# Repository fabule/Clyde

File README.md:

Clyde
======
Clyde is a lamp with a lot of personality that you can adapt, play with, and truly call your own. Clyde is open source and Arduino-compatible.  You can change how Clyde reacts to his environment by inserting personality modules on his main controller board. You can also change how Clyde behaves by reprogramming his firmware using the standard Arduino IDE.

For more information, see the website at: http://www.fabule.com or the forum at: http://fabule.com/forum/

To report a bug in the hardware or software, go to:
http://github.com/fabule/Clyde/issues

Installation
------------

The Clyde firmware is divided into three parts: bootloader, library, and sketch.

You can find the Clyde library in /software/arduino/libraries/. Place the "Clyde" library folder inside your Arduino "librairies" folder. This contains the majority of the code that controls Clyde. If you are not sure about how to install an Arduino library, you can find instructions here: http://arduino.cc/en/Guide/Libraries

When the library is in place, you can look for the sketch in /software/arduino/libraries/Clyde/Examples/ClydeOriginal. This sketch does not contain much, but it is a good place to start playing with Clyde's behaviors.

If you are using Windows, you'll need to install Clyde's driver. Find installers for 32-bit and 64-bit in /software/arduino/drivers/.  Double-click the driver that matches your needs.

Before you open your Arduino IDE, you'll need to copy one more folder. This step will add Clyde as a device under the "Tools > Board menu". First, if you do not have a "hardware" folder at the same level as your Arduino "librairies" folder, time to create one. Browse to the "hardware" folder in /software/arduino/hardware/ and open the subfolder that matches the version of your Arduino IDE, 1.0.5 or 1.5. Inside you'll find a "fabule" folder. Copy the "fabule" folder, inside the Arduino "hardware" folder you just created.

At this point, you should be ready to compile and upload Clyde's firmware. Connect Clyde to your computer using the USB cable.  Open the "ClydeFirmware" sketch in your Arduino IDE under "File > Examples > Clyde > ClydeOriginal" . Select Clyde under the "Tools > Board" menu, and the port assigned to Clyde under "Tools > Serial" Port. Press "Upload", and the firmware should compile and upload into Clyde.

If you want to make modifications to the bootloader, please refer to the information found here: https://github.com/fabule/Clyde/tree/master/software/arduino/bootloaders/caterina

Configurations
--------------

### Using `TimeAlarms` library to enable alarms

The `Time` and `TimeAlarms` libraries provide functionality to set/get the time on an arduino and enable repeated or single alarms. An example configuration to use Clyde as an *alarm clock* is given in `/software/arduino/libraries/Clyde/Examples/ClydeTimeAlarm.ino`. This firmware can be uploaded instead of the `ClydeOriginal` firmware above by loading it under "File > Examples > Clyde > ClideTimeAlarms" and following the steps described above to compile and upload the firmware. The essential configuration steps for this alternative firmware are to set the time and to define an alarm. Without any additional hardware, the time has to be set manually in and the firmware has to be uploaded to Clyde each time Clyde is detached from the power source. In principle, the `Time` and `TimeAlarms` would allow to synchronize the arduino time e.g. with internet time over a Wifi shield.

### Using Clyde without the eye

The eye of some Clydes can become quite buggy after some time. Thus, the preprocessor variable `ENABLE_EYE` has been included, that, if not defined allows to switch the lights by touching one of the legs of Clyde (requires the TouchyFeely module). The `ENABLE_EYE` can be set in the `Clyde.h` file, the leg that is to be used as a switch can be defined with the `LEG_SWITCH` variable in `ClydeTouchyFeely.cpp`.

Credits
-------
Clyde is an open source project manage by Fabule Fabrications in Montréal, Québec, Canada.

Clyde is based on the Arduino project, see the website at: http://arduino.cc

Arduino uses the GNU avr-gcc toolchain, avrdude, avr-libc, and code from
Processing and Wiring, LUFA, and i2cdevlib.

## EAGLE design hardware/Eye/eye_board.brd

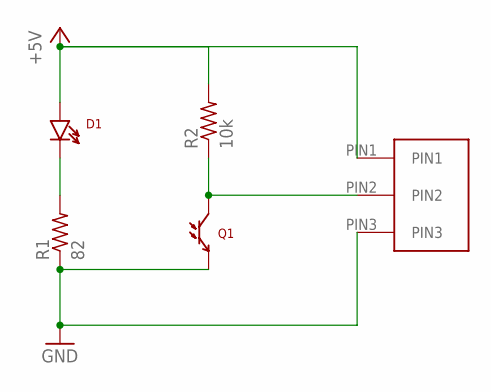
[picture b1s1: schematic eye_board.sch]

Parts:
3PIN_CONN: XH_JST_CONN_3POS_TOP
D1: LTE-302
Q1: LTR-301
R1: 82; R0603
R2: 10k; R0805

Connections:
+5V: 3PIN_CONN.PIN1, D1.A, R2.2
GND: 3PIN_CONN.PIN3, Q1.E, R1.1
unnamed: D1.C, R1.2
unnamed: 3PIN_CONN.PIN2, Q1.C, R2.1

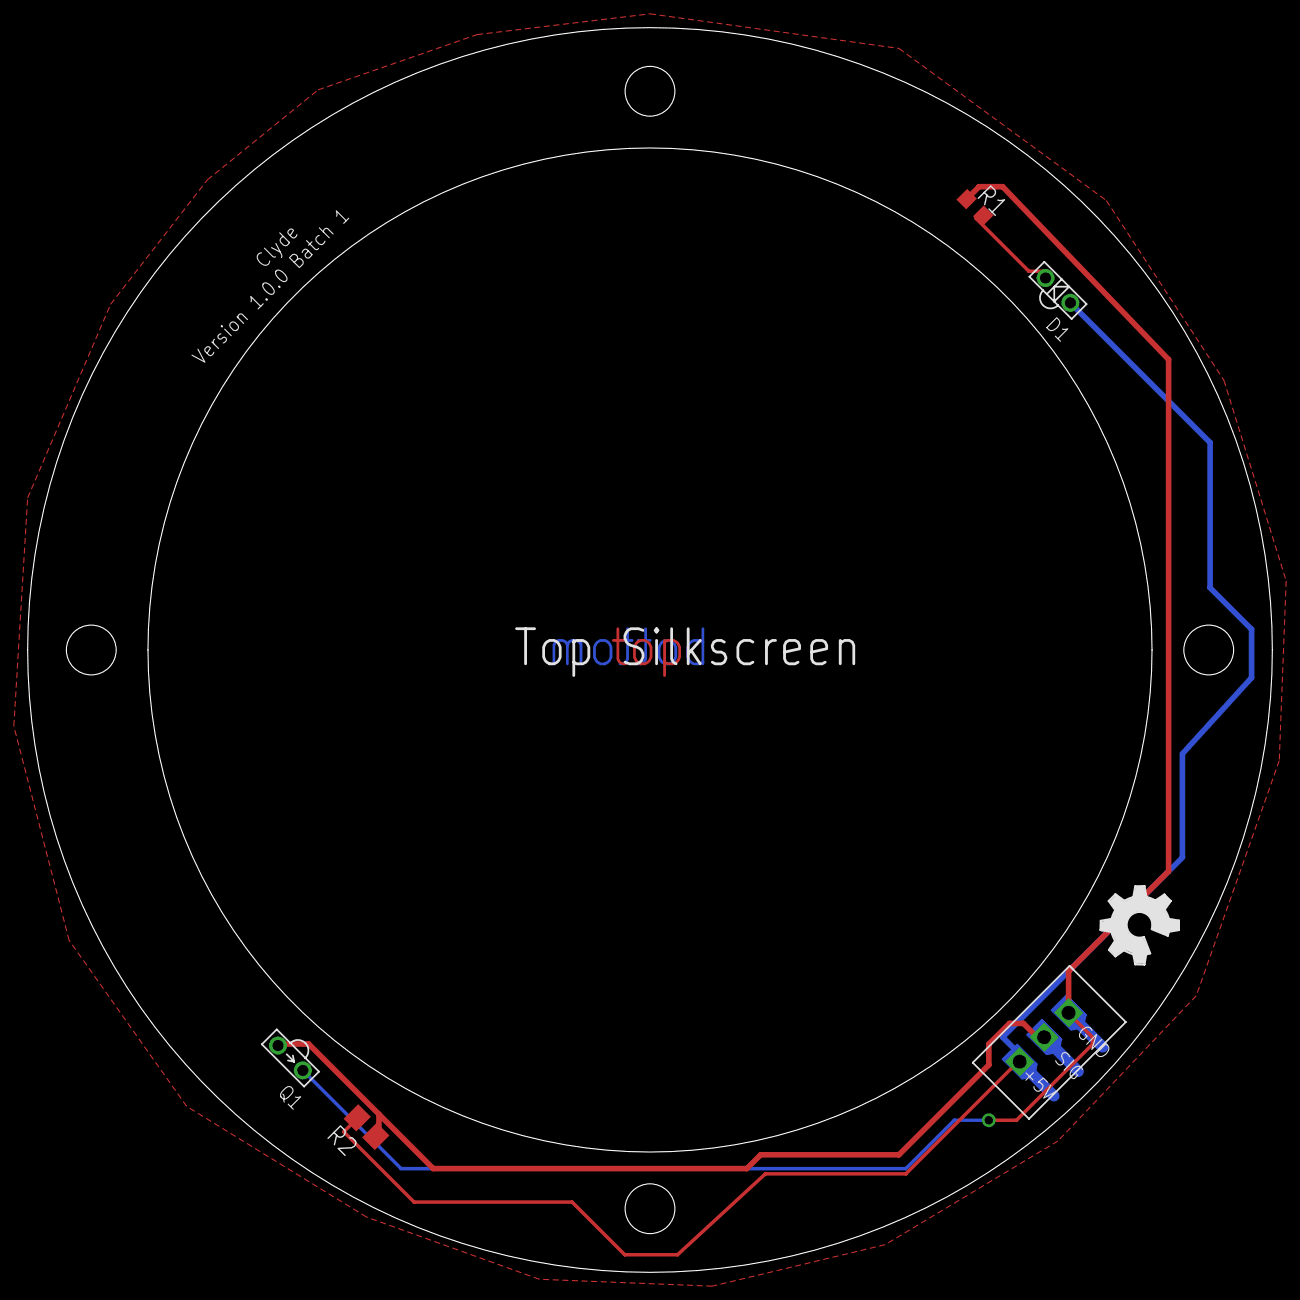
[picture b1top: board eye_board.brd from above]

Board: 2 copper layers, 90.0 x 90.0 mm, 6 parts (0 on the bottom side), 4 nets.

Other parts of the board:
U$2: OSHW_FILLX200_NOTEXT

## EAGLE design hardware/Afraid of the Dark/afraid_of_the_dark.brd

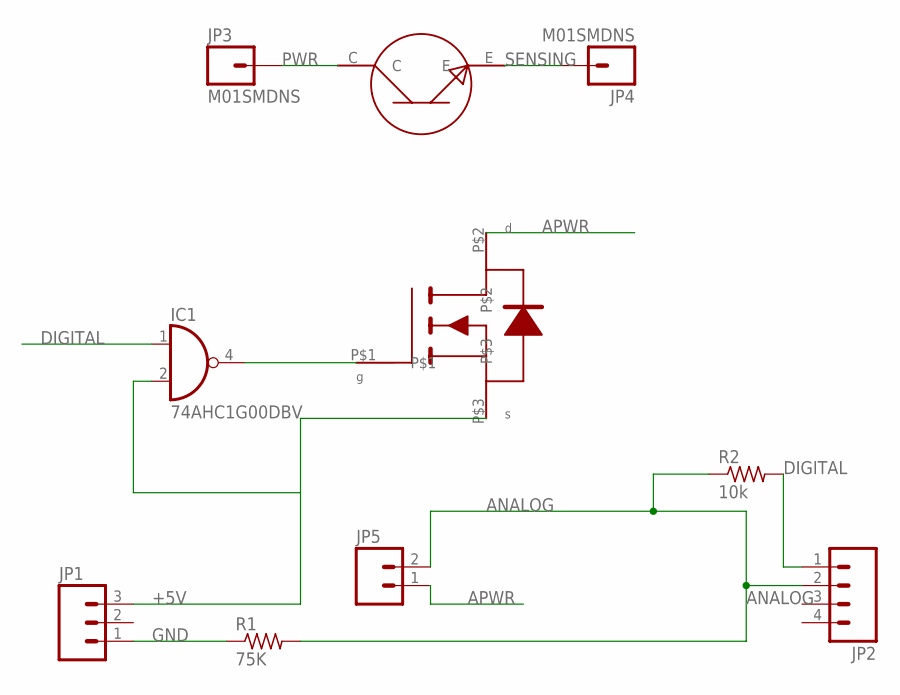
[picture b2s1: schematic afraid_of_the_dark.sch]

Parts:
IC1: 74AHC1G00DBV; SOT23-5
JP1: M03PTH; 1X03
JP2: M04PTH; 1X04
JP3, JP4: M01SMDNS; 1X01NS
JP5: M023.5MM; SCREWTERMINAL-3.5MM-2
R1: 75K; R0805
R2: 10k; R0805
U1: AMBIENT_LIGHT_SENSOR
U3: SI2302DS_MOSFET

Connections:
+5V: IC1.2 (I1), JP1.3, U3.P$3
ANALOG: JP2.2, JP5.2, R1.2, R2.1
APWR: JP5.1, U3.P$2
DIGITAL: IC1.1 (I0), JP2.1, R2.2
GND: IC1.3 (GND), JP1.1, R1.1
unnamed: IC1.4 (O), U3.P$1
PWR: JP3.1, U1.C
SENSING: JP4.1, U1.E
VCC: IC1.5 (VCC)

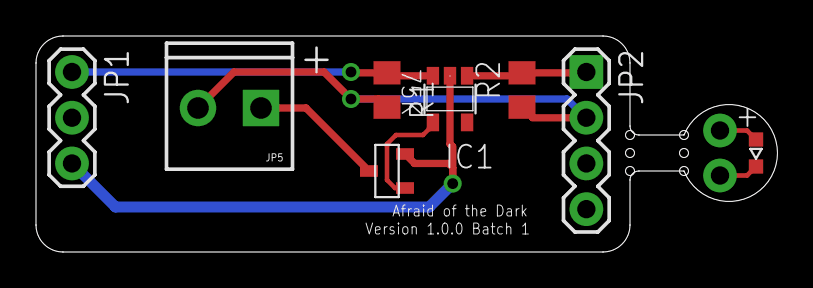
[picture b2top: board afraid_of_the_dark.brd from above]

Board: 2 copper layers, 41.2 x 12.0 mm, 11 parts (1 on the bottom side), 8 nets.

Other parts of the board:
U$2: OSHW_FILLX200_NOTEXT

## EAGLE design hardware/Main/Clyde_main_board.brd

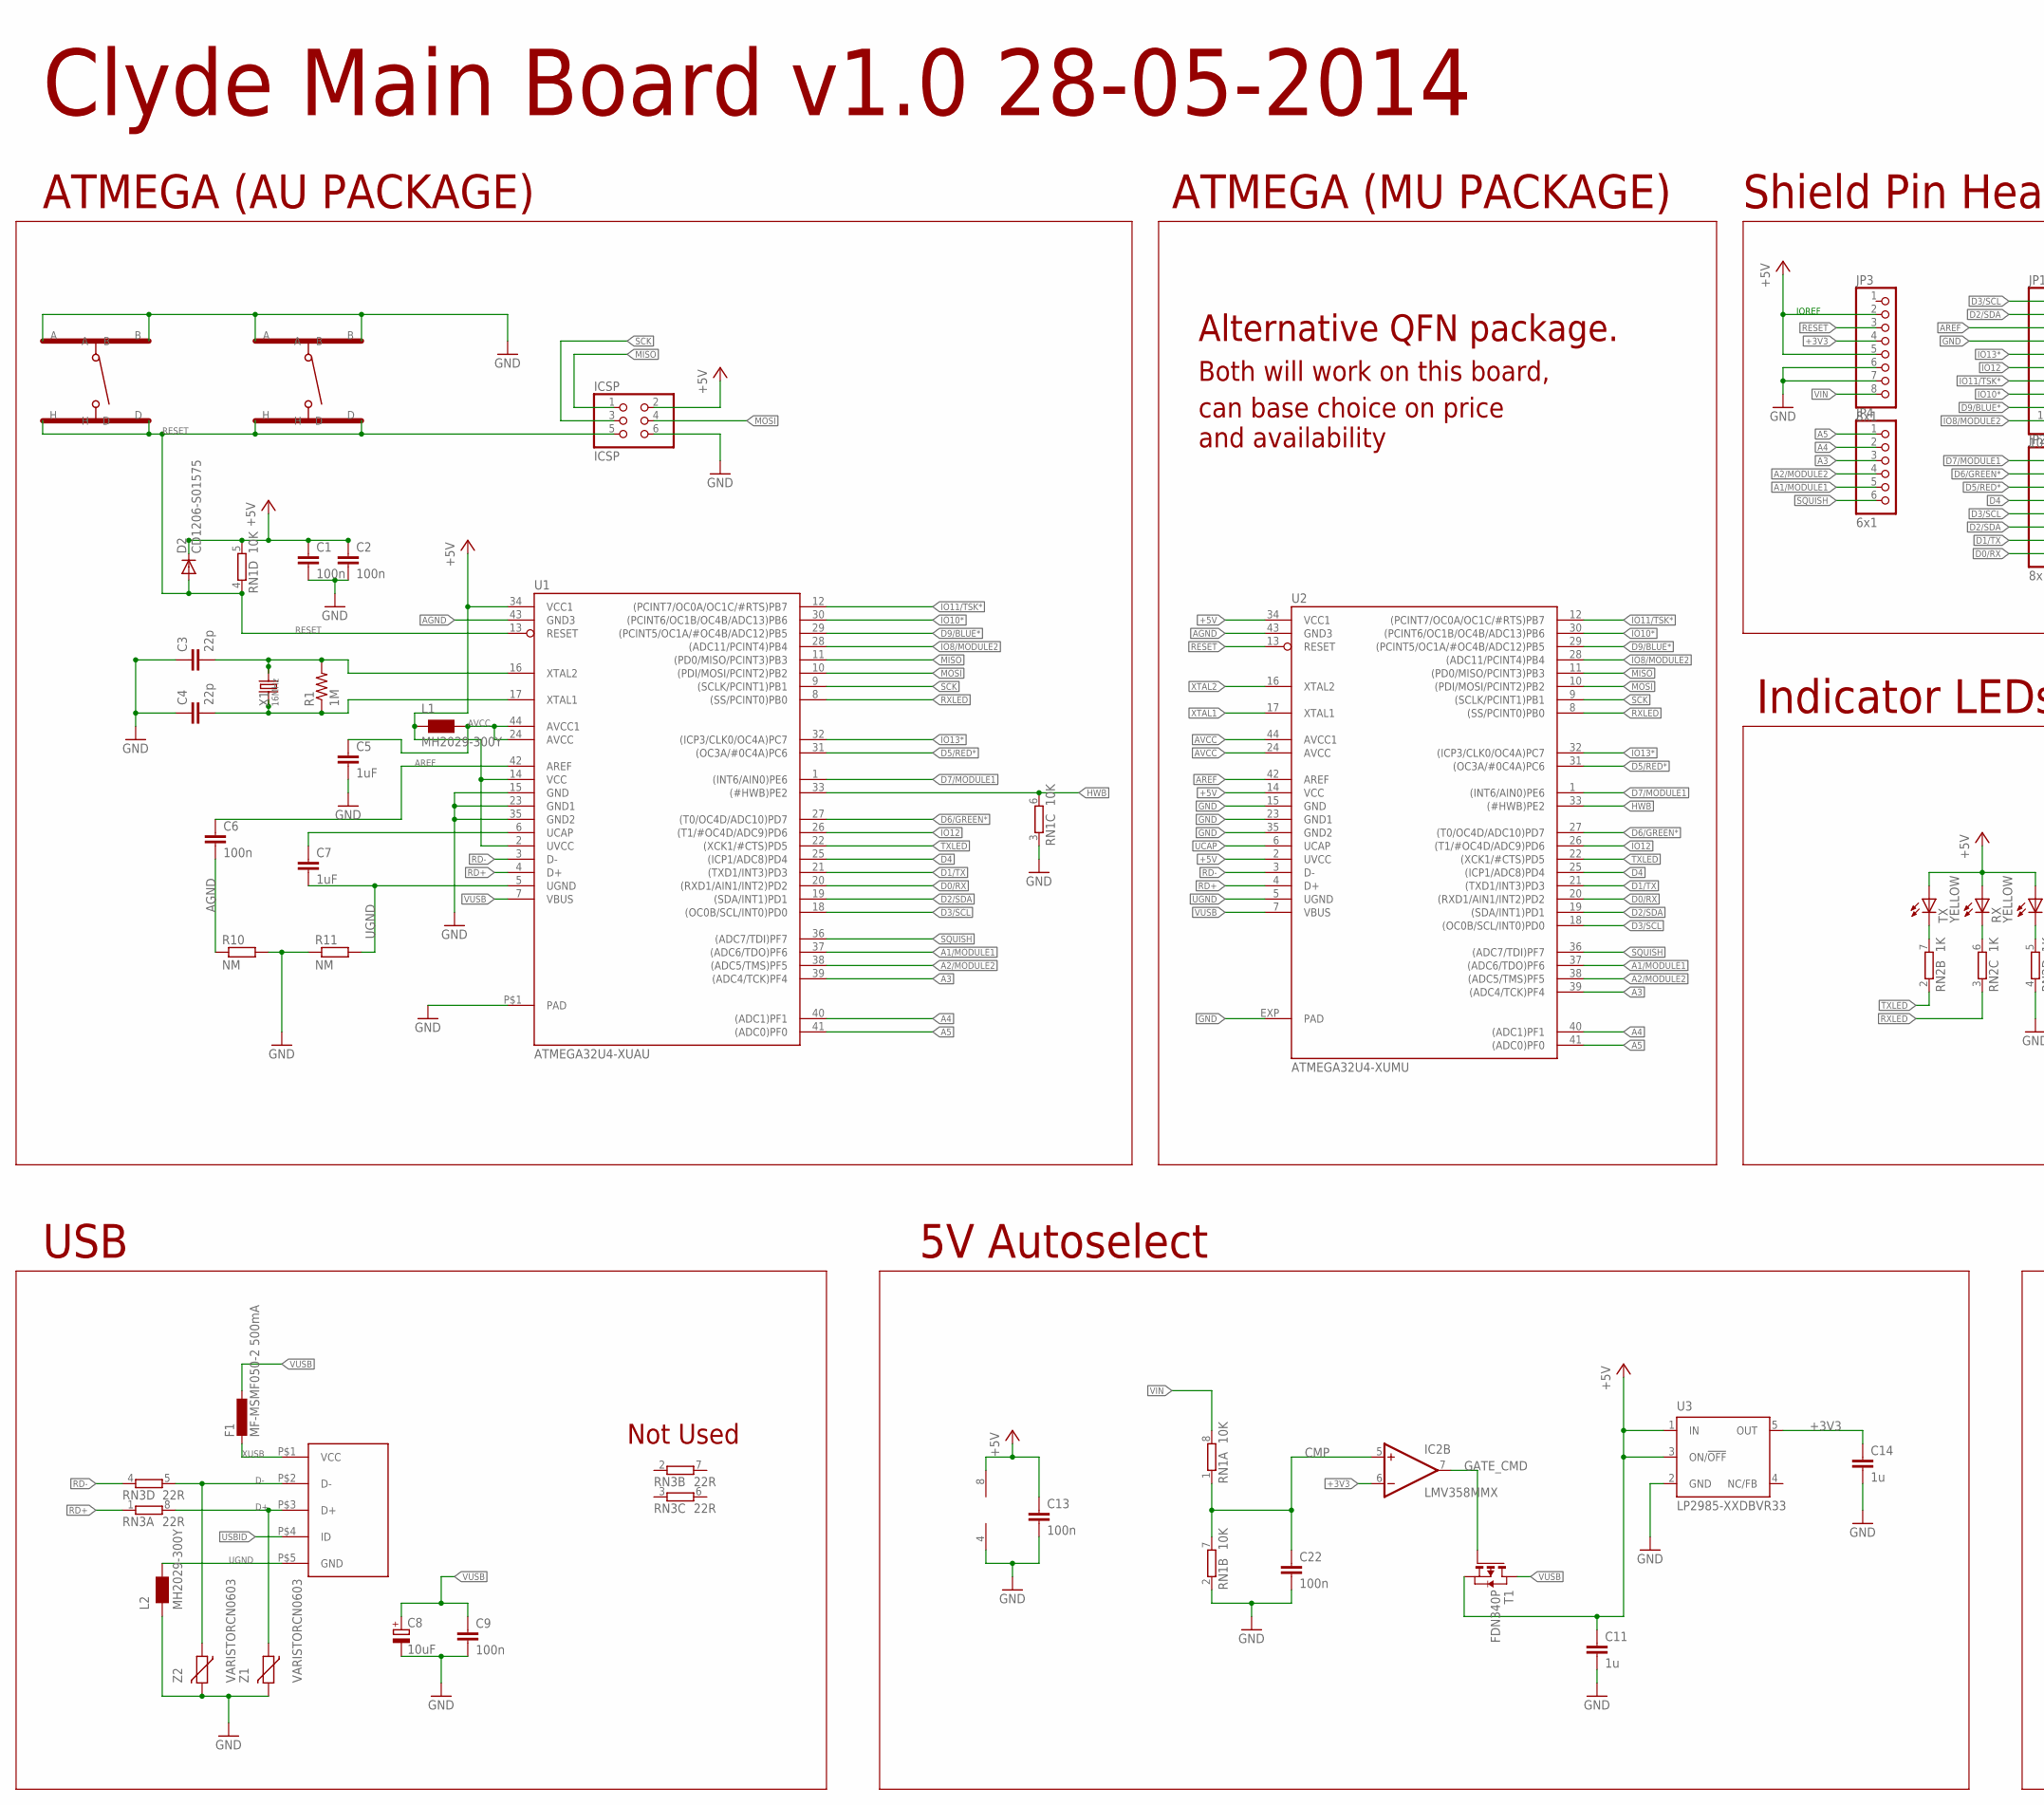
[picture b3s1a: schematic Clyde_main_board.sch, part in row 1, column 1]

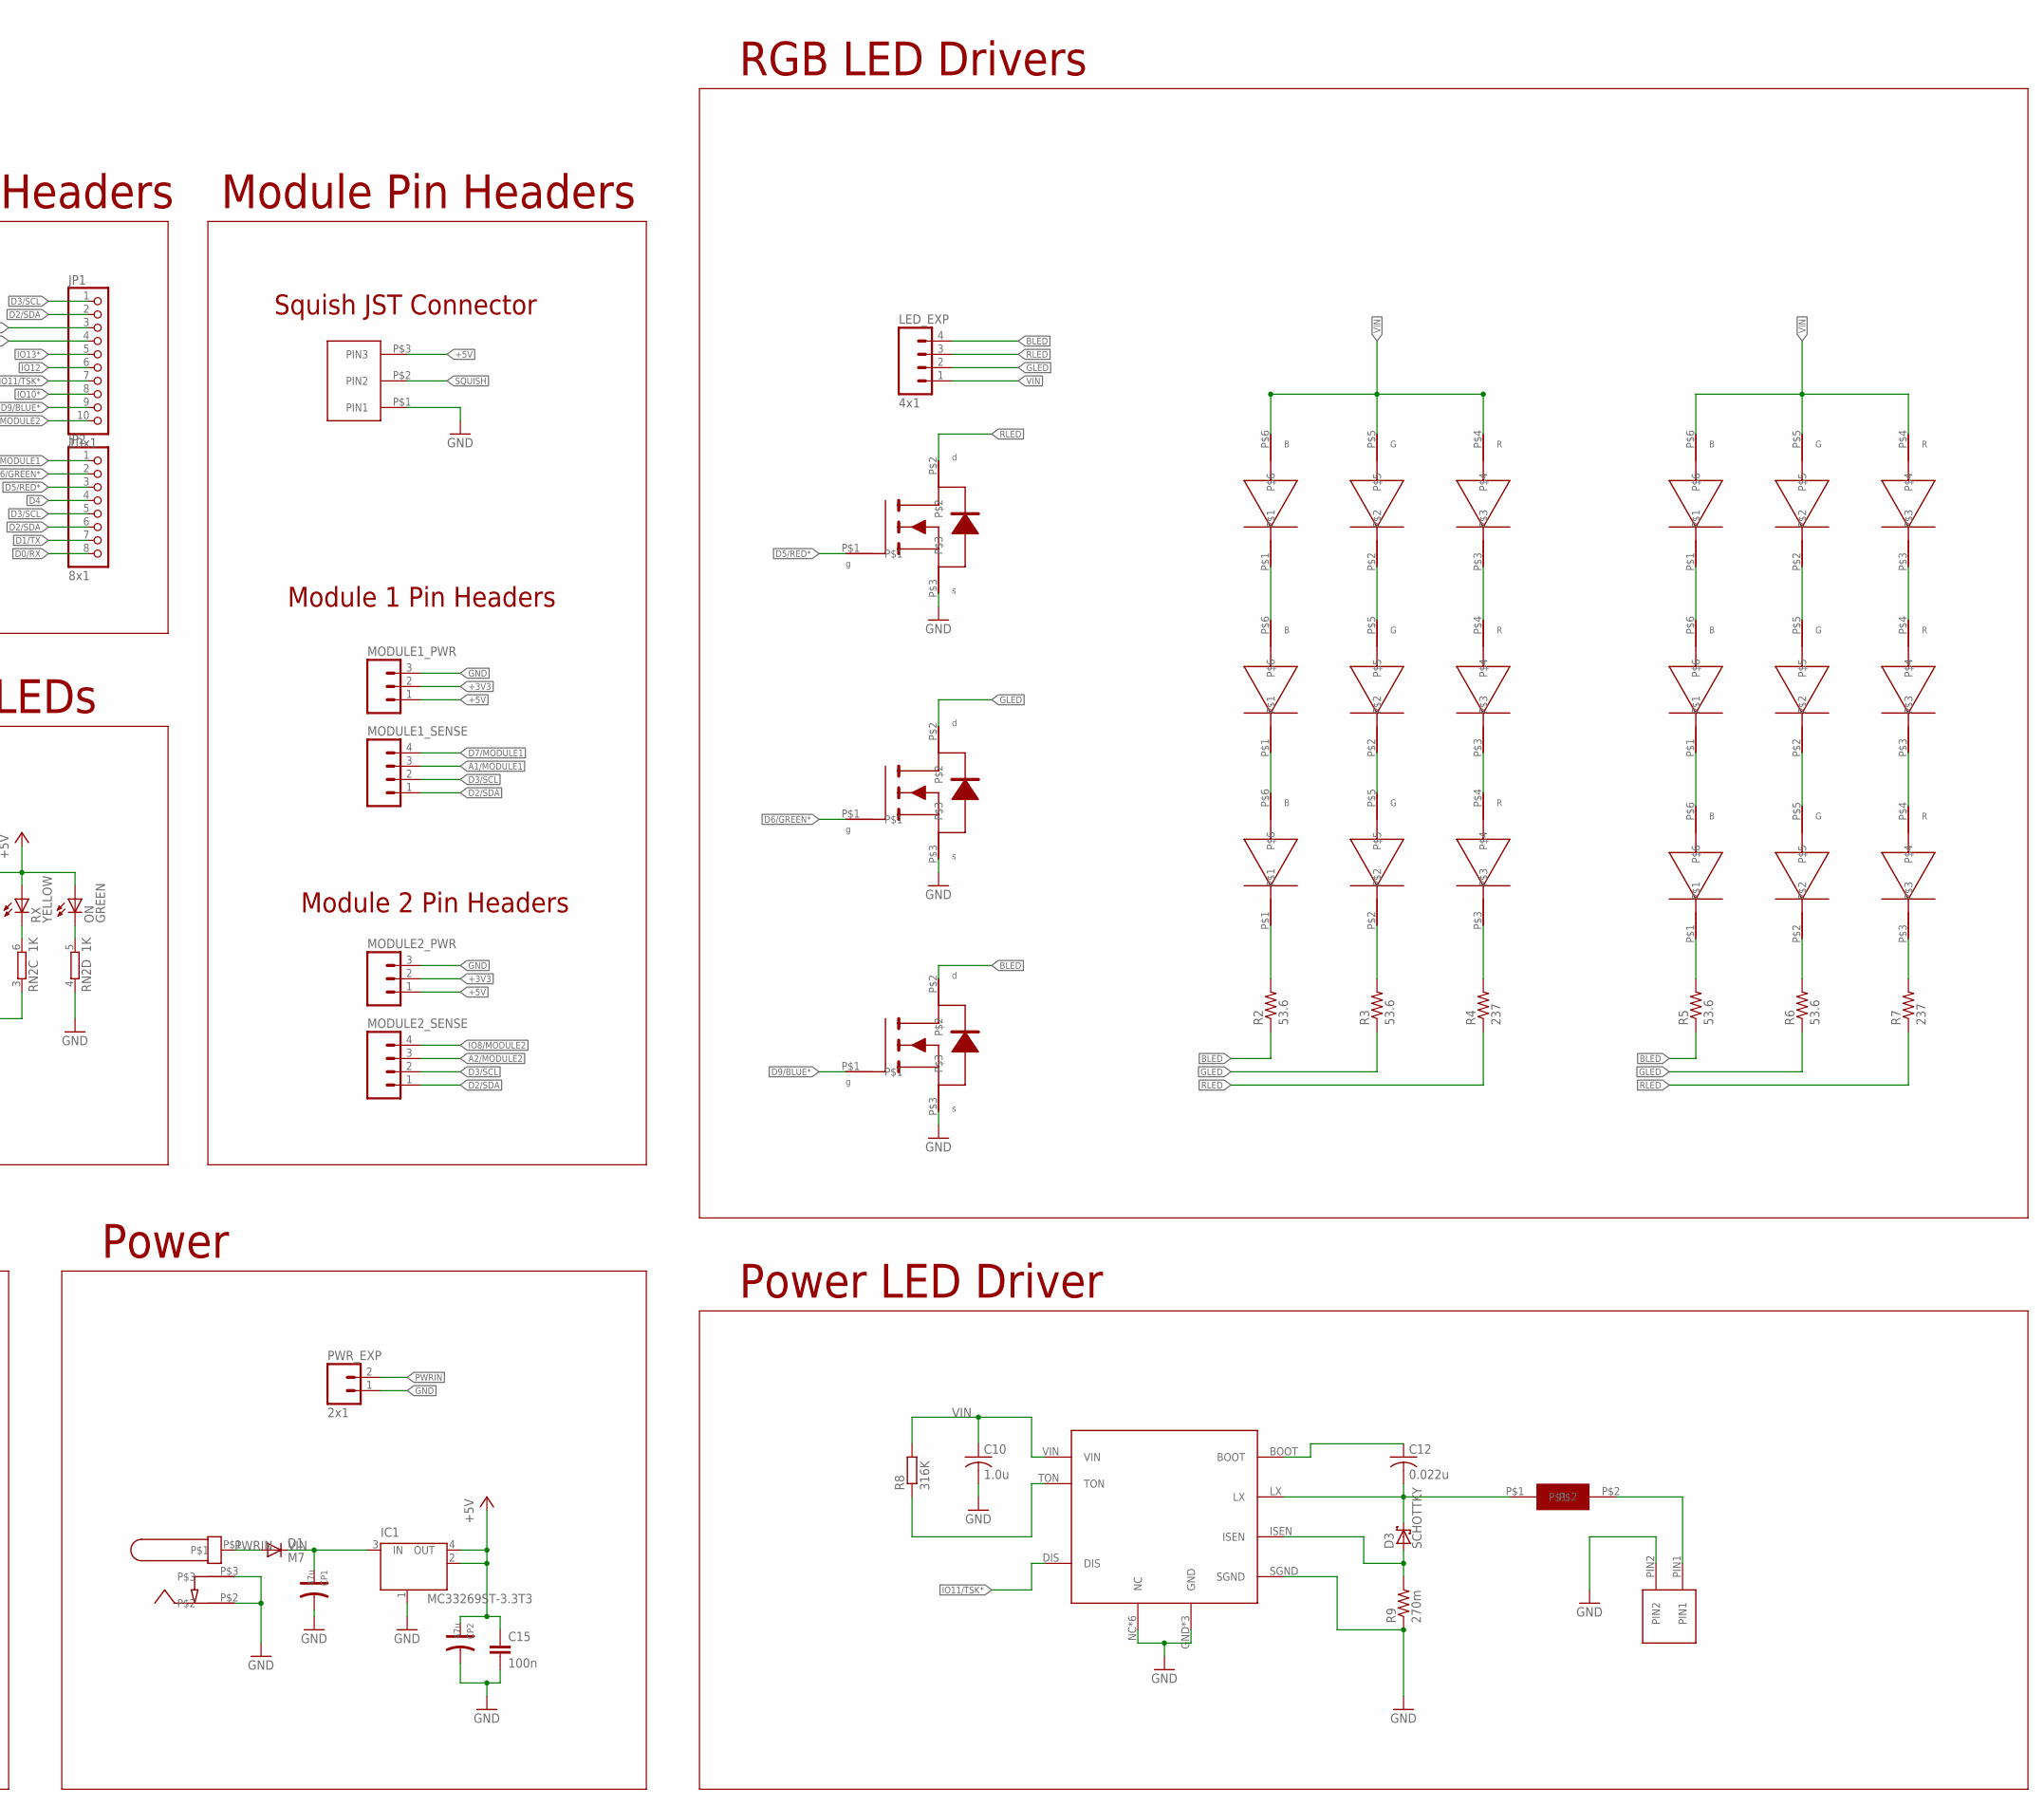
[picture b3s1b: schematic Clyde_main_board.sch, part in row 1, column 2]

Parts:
2PIN_CONN: XH_JST_CONN_2POS_TOP
C1, C2, C6, C9, C13, C15, C22: 100n; C0603-ROUND
C3, C4: 22p; C0603-ROUND
C5, C7: 1uF; C0603-ROUND
C8: 10uF; SMC_B
C10: 1.0u; C1210
C11, C14: 1u; C0603-ROUND
C12: 0.022u; C0805
CP1, CP2: 47u; ELECTRO-SMD-C-6MM
D1: M7; SMB
D2: CD1206-S01575; MINIMELF
D3: SCHOTTKY; SMB
F1: MF-MSMF050-2 500mA; L1812
IC1: MC33269ST-3.3T3; SOT223
IC2: LMV358MMX; MSOP08
ICSP: ICSP; 2X03
IR_CONNECT: XH_JST_CONN_3POS_SIDE_SMT
I_LEDDRIVER: TAIYO_YUDEN_6045_INDUCTOR
J1: MOLEX_VERT_MINIUSB
JP1: 10x1; 1X10
JP2, JP3: 8x1; 1X08
JP4: 6x1; 1X06
L1, L2: MH2029-300Y; 0805
LED_EXP: 4x1; 1X04_LONGPADS
MODULE1_PWR, MODULE2_PWR: M03PTH; 1X03
MODULE1_SENSE, MODULE2_SENSE: M04PTH; 1X04
ON: GREEN; CHIPLED_0603
PWR_EXP: 2x1; SCREWTERMINAL-3.5MM-2
PWR_JACK: VERT_PWRJACK_PJ-006A_CUIINC
R1: 1M; 0805
R2, R3, R5, R6: 53.6; R0603
R4, R7: 237; R0603
R8: 316K; R0603-ROUND
R9: 270m; R0805
R10, R11: NM; R0402_NM
RGB1, RGB2, RGB3, RGB4, RGB5, RGB6: HANGZHOU_MULTICOLOR_3535WSA; HANGZHOU_MULTCOLOR_3535WSZ
RN1: 10K; CAY16
RN2: 1K; CAY16
RN3: 22R; CAY16
RST, RST1: COMAX_MINISWITCH
RX: YELLOW; CHIPLED_0603
T1: FDN340P; SOT-23
TBLUE: SI2302DS_MOSFET
TGREEN: SI2302DS_MOSFET
TRED: SI2302DS_MOSFET
TX: YELLOW; CHIPLED_0603
U1: ATMEGA32U4-XUAU; TQFP44-PAD
U2: ATMEGA32U4-XUMU; QFN44ML7X7
U3: LP2985-XXDBVR33; SOT23-DBV
U4: ALLEGRO_A6210
X1: 16MHz; XTAL_THRU_SMT
Z1, Z2: VARISTORCN0603; CT/CN0603

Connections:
+3V3: C14.1, IC2.6 (-IN), JP3.4, MODULE1_PWR.2, MODULE2_PWR.2, U3.5 (OUT)
+5V: C1.1, C2.1, C11.1, C13.1, C15.1, CP2.+, D2.C, IC1.2 (OUT), IC1.4 (OUT), IC2.8 (V+), ICSP.2, IR_CONNECT.P$3 (PIN3), JP3.2, JP3.5, L1.1, MODULE1_PWR.1, MODULE2_PWR.1, ON.A, RN1.5 (2), RX.A, T1.2 (S), TX.A, U1.2 (UVCC), U1.14 (VCC), U1.34 (VCC1), U2.2 (UVCC), U2.14 (VCC), U2.34 (VCC1), U3.1 (IN), U3.3 (ON/!OFF)
A1/MODULE1: JP4.5, MODULE1_SENSE.3, U1.37 ((ADC6/TDO)PF6), U2.37 ((ADC6/TDO)PF6)
A2/MODULE2: JP4.4, MODULE2_SENSE.3, U1.38 ((ADC5/TMS)PF5), U2.38 ((ADC5/TMS)PF5)
A3: JP4.3, U1.39 ((ADC4/TCK)PF4), U2.39 ((ADC4/TCK)PF4)
A4: JP4.2, U1.40 ((ADC1)PF1), U2.40 ((ADC1)PF1)
A5: JP4.1, U1.41 ((ADC0)PF0), U2.41 ((ADC0)PF0)
AGND: C6.2, R10.1, U1.43 (GND3), U2.43 (GND3)
AREF: C6.1, JP1.3, U1.42 (AREF), U2.42 (AREF)
AVCC: C5.1, L1.2, U1.24 (AVCC), U1.44 (AVCC1), U2.24 (AVCC), U2.44 (AVCC1)
BLED: LED_EXP.4, R2.1, R5.1, TBLUE.P$2
CMP: C22.1, IC2.5 (+IN), RN1.1, RN1.7 (2)
D0/RX: JP2.8, U1.20 ((RXD1/AIN1/INT2)PD2), U2.20 ((RXD1/AIN1/INT2)PD2)
D1/TX: JP2.7, U1.21 ((TXD1/INT3)PD3), U2.21 ((TXD1/INT3)PD3)
D2/SDA: JP1.2, JP2.6, MODULE1_SENSE.1, MODULE2_SENSE.1, U1.19 ((SDA/INT1)PD1), U2.19 ((SDA/INT1)PD1)
D3/SCL: JP1.1, JP2.5, MODULE1_SENSE.2, MODULE2_SENSE.2, U1.18 ((OC0B/SCL/INT0)PD0), U2.18 ((OC0B/SCL/INT0)PD0)
D4: JP2.4, U1.25 ((ICP1/ADC8)PD4), U2.25 ((ICP1/ADC8)PD4)
D5/RED*: JP2.3, TRED.P$1, U1.31 ((OC3A/#0C4A)PC6), U2.31 ((OC3A/#0C4A)PC6)
D6/GREEN*: JP2.2, TGREEN.P$1, U1.27 ((T0/OC4D/ADC10)PD7), U2.27 ((T0/OC4D/ADC10)PD7)
D7/MODULE1: JP2.1, MODULE1_SENSE.4, U1.1 ((INT6/AIN0)PE6), U2.1 ((INT6/AIN0)PE6)
D9/BLUE*: JP1.9, TBLUE.P$1, U1.29 ((PCINT5/OC1A/#OC4B/ADC12)PB5), U2.29 ((PCINT5/OC1A/#OC4B/ADC12)PB5)
D+: J1.P$3 (D+), RN3.8 (2), Z1.1
D-: J1.P$2 (D-), RN3.5 (2), Z2.1
GATE_CMD: IC2.7 (OUT), T1.3 (G)
GLED: LED_EXP.2, R3.1, R6.1, TGREEN.P$2
GND: 2PIN_CONN.PIN2, C1.2, C2.2, C3.1, C4.1, C5.2, C8.-, C9.2, C10.2, C11.2, C13.2, C14.2, C15.2, C22.2, CP1.-, CP2.-, IC1.1 (GND/ADJ), IC2.4 (V-), ICSP.6, IR_CONNECT.P$1 (PIN1), JP1.4, JP3.6, JP3.7, L2.1, MODULE1_PWR.3, MODULE2_PWR.3, PWR_EXP.1, PWR_JACK.P$2, PWR_JACK.P$3, R9.1, R10.2, R11.1, RN1.2 (1), RN1.3 (1), RN2.4 (1), RST.A, RST.B, RST1.A, RST1.B, TBLUE.P$3, TGREEN.P$3, TRED.P$3, U1.15 (GND), U1.23 (GND1), U1.35 (GND2), U1.P$1 (PAD), U2.15 (GND), U2.23 (GND1), U2.35 (GND2), U2.EXP (PAD), U3.2 (GND), U4.GND, U4.GND1 (GND), U4.GND2 (GND), U4.NC, U4.NC1 (NC), U4.NC2 (NC), U4.NC3 (NC), U4.NC4 (NC), U4.NC5 (NC), U4.SGND, Z1.2, Z2.2
HWB: RN1.6 (2), U1.33 ((#HWB)PE2), U2.33 ((#HWB)PE2)
IO8/MODULE2: JP1.10, MODULE2_SENSE.4, U1.28 ((ADC11/PCINT4)PB4), U2.28 ((ADC11/PCINT4)PB4)
IO10*: JP1.8, U1.30 ((PCINT6/OC1B/OC4B/ADC13)PB6), U2.30 ((PCINT6/OC1B/OC4B/ADC13)PB6)
IO11/TSK*: JP1.7, U1.12 ((PCINT7/OC0A/OC1C/#RTS)PB7), U2.12 ((PCINT7/OC0A/OC1C/#RTS)PB7), U4.DIS
IO12: JP1.6, U1.26 ((T1/#OC4D/ADC9)PD6), U2.26 ((T1/#OC4D/ADC9)PD6)
IO13*: JP1.5, U1.32 ((ICP3/CLK0/OC4A)PC7), U2.32 ((ICP3/CLK0/OC4A)PC7)
MISO: ICSP.1, U1.11 ((PD0/MISO/PCINT3)PB3), U2.11 ((PD0/MISO/PCINT3)PB3)
MOSI: ICSP.4, U1.10 ((PDI/MOSI/PCINT2)PB2), U2.10 ((PDI/MOSI/PCINT2)PB2)
unnamed: R8.1, U4.TON
unnamed: D3.A, R9.2, U4.ISEN
unnamed: C12.1, U4.BOOT
unnamed: C12.2, D3.C, I_LEDDRIVER.P$1, U4.LX
unnamed: RN2.7 (2), TX.C
unnamed: RN2.6 (2), RX.C
unnamed: ON.C, RN2.5 (2)
unnamed: R2.2, RGB3.P$1
unnamed: 2PIN_CONN.PIN1, I_LEDDRIVER.P$2
unnamed: R3.2, RGB3.P$2
unnamed: R4.2, RGB3.P$3
unnamed: RGB2.P$1, RGB3.P$6
unnamed: RGB2.P$2, RGB3.P$5
unnamed: RGB2.P$3, RGB3.P$4
unnamed: R5.2, RGB6.P$1
unnamed: R6.2, RGB6.P$2
unnamed: R7.2, RGB6.P$3
unnamed: RGB5.P$1, RGB6.P$6
unnamed: RGB5.P$2, RGB6.P$5
unnamed: RGB5.P$3, RGB6.P$4
unnamed: RGB4.P$3, RGB5.P$4
unnamed: RGB4.P$2, RGB5.P$5
unnamed: RGB4.P$1, RGB5.P$6
unnamed: RGB1.P$3, RGB2.P$4
unnamed: RGB1.P$2, RGB2.P$5
unnamed: RGB1.P$1, RGB2.P$6
PWRIN: D1.A, PWR_EXP.2, PWR_JACK.P$1
RD+: RN3.1, U1.4 (D+), U2.4 (D+)
RD-: RN3.4 (1), U1.3 (D-), U2.3 (D-)
RESET: D2.A, ICSP.5, JP3.3, RN1.4 (1), RST.D, RST.H, RST1.D, RST1.H, U1.13 (RESET), U2.13 (RESET)
RLED: LED_EXP.3, R4.1, R7.1, TRED.P$2
RXLED: RN2.3 (1), U1.8 ((SS/PCINT0)PB0), U2.8 ((SS/PCINT0)PB0)
SCK: ICSP.3, U1.9 ((SCLK/PCINT1)PB1), U2.9 ((SCLK/PCINT1)PB1)
SQUISH: IR_CONNECT.P$2 (PIN2), JP4.6, U1.36 ((ADC7/TDI)PF7), U2.36 ((ADC7/TDI)PF7)
TXLED: RN2.2 (1), U1.22 ((XCK1/#CTS)PD5), U2.22 ((XCK1/#CTS)PD5)
UCAP: C7.1, U1.6 (UCAP), U2.6 (UCAP)
UGND: C7.2, J1.P$5 (GND), L2.2, R11.2, U1.5 (UGND), U2.5 (UGND)
USBID: J1.P$4 (ID)
VIN: C10.1, CP1.+, D1.C, IC1.3 (IN), JP3.8, LED_EXP.1, R8.2, RGB1.P$4, RGB1.P$5, RGB1.P$6, RGB4.P$4, RGB4.P$5, RGB4.P$6, RN1.8 (2), U4.VIN
VUSB: C8.+, C9.1, F1.1, T1.1 (D), U1.7 (VBUS), U2.7 (VBUS)
XTAL1: C4.2, R1.1, U1.17 (XTAL1), U2.17 (XTAL1), X1.1, X1.P$1 (1)
XTAL2: C3.2, R1.2, U1.16 (XTAL2), U2.16 (XTAL2), X1.2, X1.P$2 (2)
XUSB: F1.2, J1.P$1 (VCC)

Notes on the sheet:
IOREF
RGB LED Drivers
Power LED Driver
ATMEGA (AU PACKAGE)
Shield Pin Headers
Module Pin Headers
Squish JST Connector
Module 1 Pin Headers
Module 2 Pin Headers
Not Used
USB
Indicator LEDs
5V Autoselect
Power
Clyde Main Board v1.0 28-05-2014
ATMEGA (MU PACKAGE)
Alternative QFN package.
Both will work on this board,
can base choice on price and availability

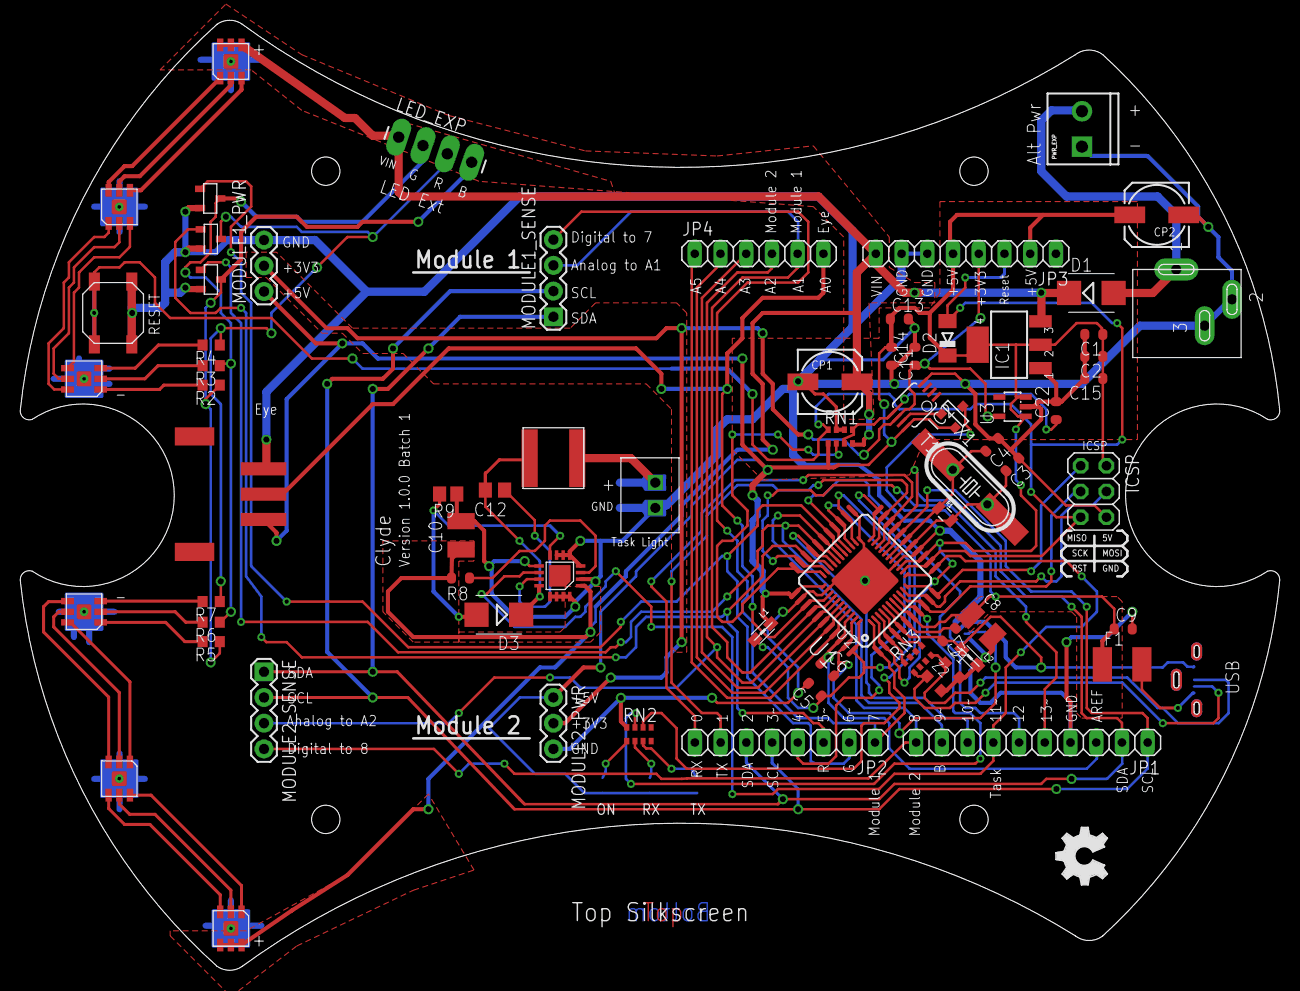
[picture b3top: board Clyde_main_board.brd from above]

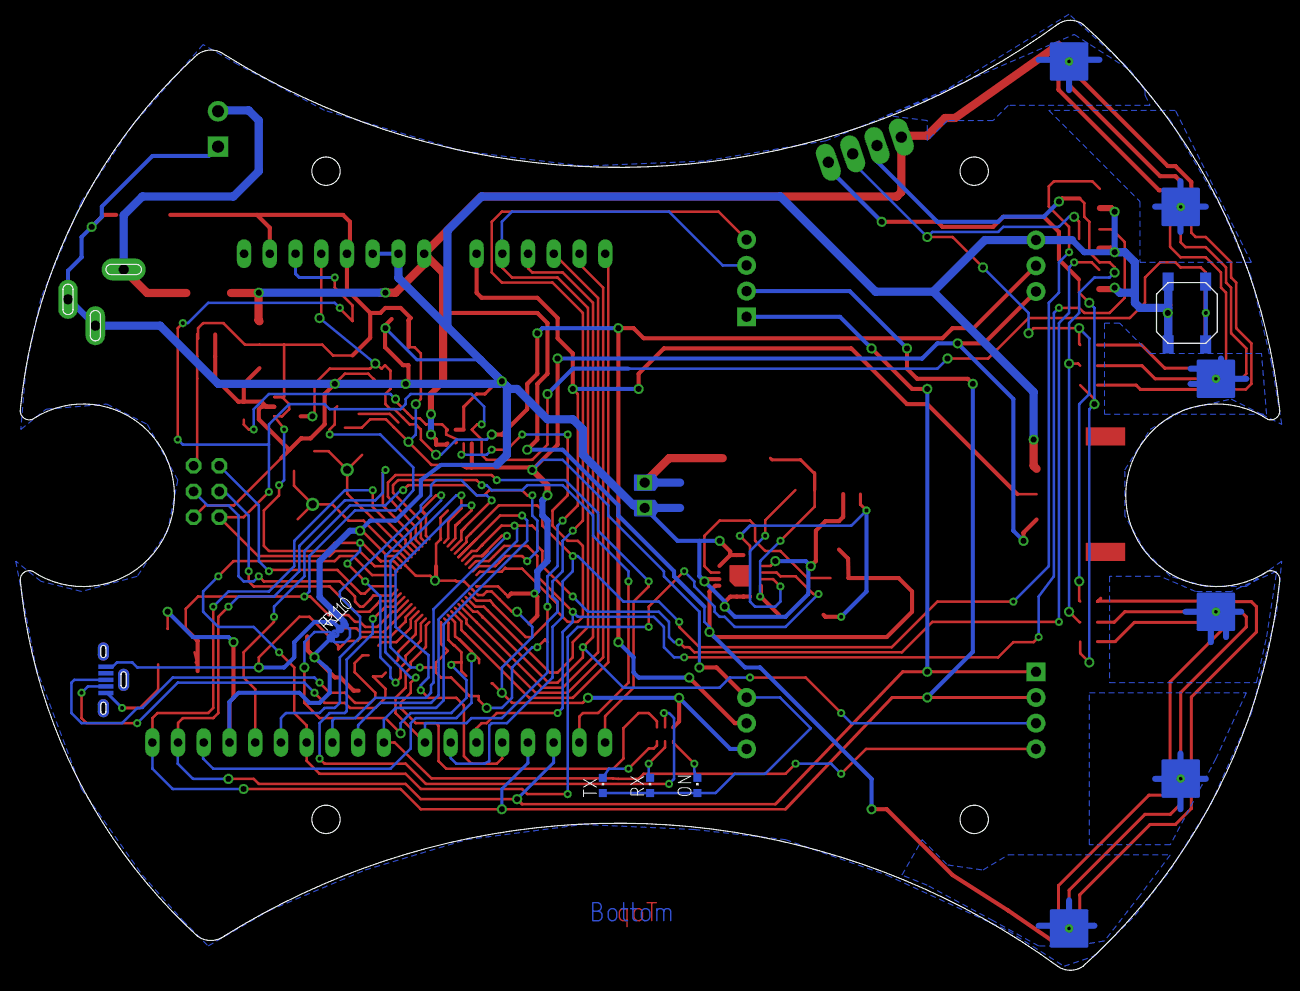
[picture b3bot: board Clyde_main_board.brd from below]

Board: 2 copper layers, 124.4 x 93.8 mm, 79 parts (7 on the bottom side), 76 nets.

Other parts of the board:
U$1: OSHW_FILLX200_NOTEXT

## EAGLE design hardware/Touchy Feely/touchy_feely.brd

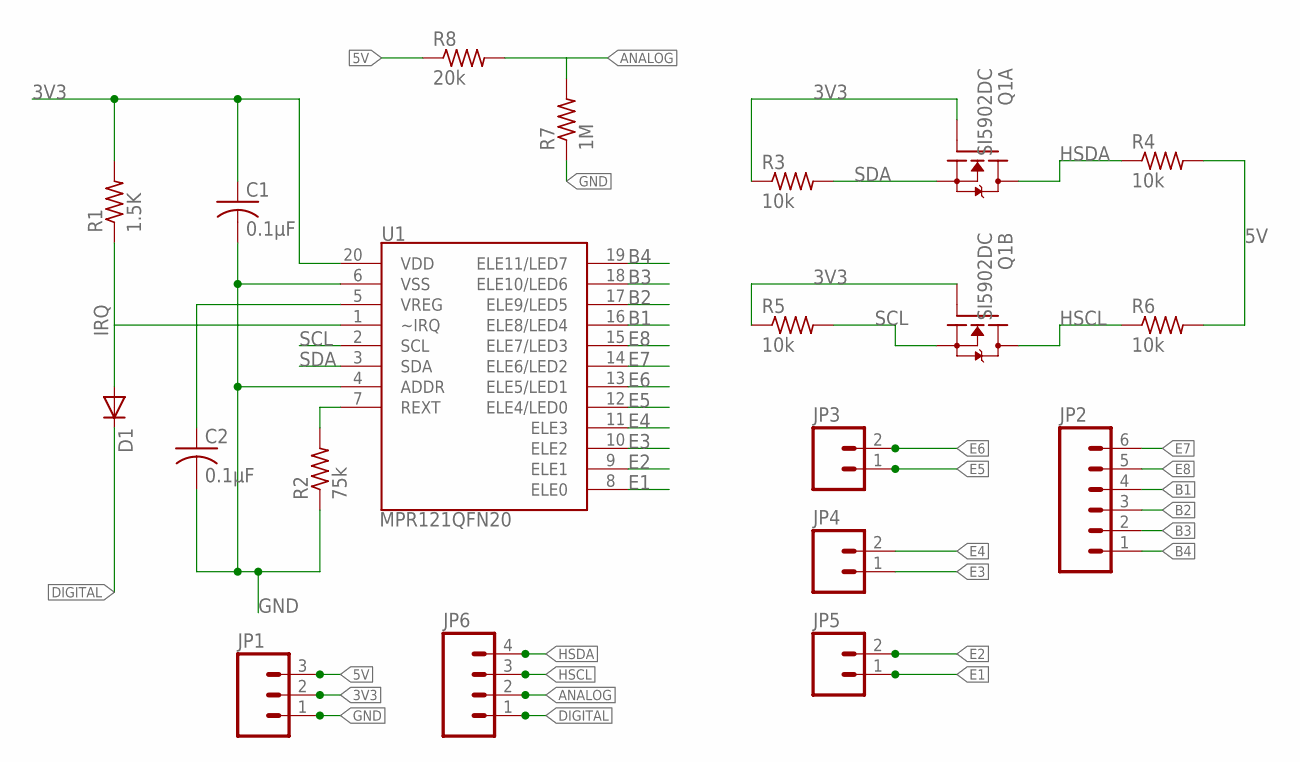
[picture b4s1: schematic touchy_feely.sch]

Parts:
C1, C2: 0.1µF; C0603K
D1: DIODE-MINIMELF; MINIMELF
JP1: M03PTH; 1X03
JP2: M06SIP; 1X06
JP3, JP4, JP5: M023.5MM; SCREWTERMINAL-3.5MM-2
JP6: M04PTH; 1X04
Q1: SI5902DC; 1206-8CHIP-FET
R1: 1.5K; M0805
R2: 75k; M0805
R3, R4, R5, R6: 10k; M0805
R7: 1M; R0805
R8: 20k; R0805
U1: MPR121QFN20; QFN-20-0.4MM

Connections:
3V3: C1.1, JP1.2, Q1.2 (G), Q1.4 (G), R1.2, R3.1, R5.1, U1.20 (VDD)
5V: JP1.3, R4.2, R6.2, R8.1
ANALOG: JP6.2, R7.2, R8.2
B1: JP2.4, U1.16 (ELE8/LED4)
B2: JP2.3, U1.17 (ELE9/LED5)
B3: JP2.2, U1.18 (ELE10/LED6)
B4: JP2.1, U1.19 (ELE11/LED7)
DIGITAL: D1.C, JP6.1
E1: JP5.1, U1.8 (ELE0)
E2: JP5.2, U1.9 (ELE1)
E3: JP4.1, U1.10 (ELE2)
E4: JP4.2, U1.11 (ELE3)
E5: JP3.1, U1.12 (ELE4/LED0)
E6: JP3.2, U1.13 (ELE5/LED1)
E7: JP2.6, U1.14 (ELE6/LED2)
E8: JP2.5, U1.15 (ELE7/LED3)
GND: C1.2, C2.2, JP1.1, R2.1, R7.1, U1.4 (ADDR), U1.6 (VSS)
HSCL: JP6.3, Q1.5 (D), Q1.6 (D), R6.1
HSDA: JP6.4, Q1.7 (D), Q1.8 (D), R4.1
IRQ: D1.A, R1.1, U1.1 (~IRQ)
unnamed: C2.1, U1.5 (VREG)
unnamed: R2.2, U1.7 (REXT)
SCL: Q1.3 (S), R5.2, U1.2 (SCL)
SDA: Q1.1 (S), R3.2, U1.3 (SDA)

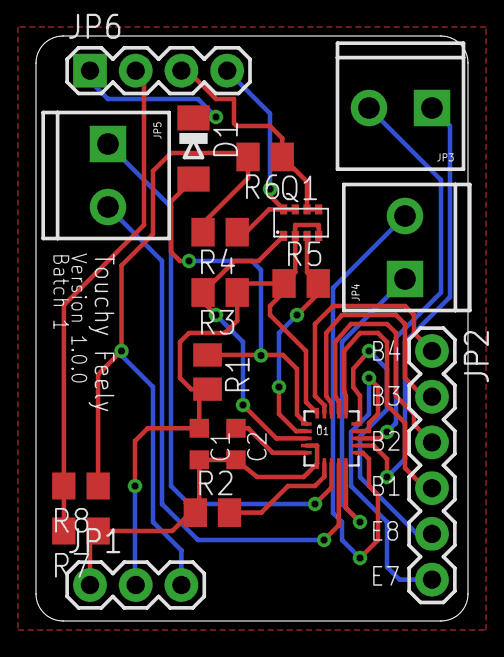
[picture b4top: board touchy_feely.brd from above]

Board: 2 copper layers, 24.0 x 32.5 mm, 20 parts (1 on the bottom side), 24 nets.

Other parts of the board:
U$2: OSHW_FILLX200_NOTEXT

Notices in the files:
parts and their libraries:
SparkFun: Licensing: CC v3.0 Share-Alike You are welcome to use this library for commercial purposes.
